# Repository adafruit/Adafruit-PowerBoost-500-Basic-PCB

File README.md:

## Adafruit PowerBoost 500 Basic PCB
<a href="http://www.adafruit.com/products/1903"><br/>
Click here to purchase one from the Adafruit shop</a>

This little DC/DC boost converter module can run from 1.8V batteries or higher, and convert that voltage to 5.2V DC for running your 5V projects. Like our popular 5V 1A USB wall adapter, we tweaked the output to be 5.2V instead of a straight-up 5.0V so that there's a little bit of 'headroom' long cables, high draw, the addition of a diode on the output if you wish, etc. The 5.2V is safe for all 5V-powered electronics like Adafruit Metro/Trinket/Gemma/ItsyBitsy, Arduino, Raspberry Pi, or BeagleBone while preventing icky brown-outs during high current draw because of USB cable resistance.

The PowerBoost 500 has at the heart a TPS61090 boost converter from TI. This boost converter chip has some really nice extras such as low battery detection, 2A internal switch, synchronous conversion, excellent efficiency, and 700KHz high-frequency operation.

These are the Eagle CAD files for the Adafruit Adafruit PowerBoost 500 Basic breakout:
----> https://www.adafruit.com/product/1903

### License

Adafruit invests time and resources providing this open source design, please support Adafruit and open-source hardware by purchasing products from [Adafruit](https://www.adafruit.com)!

All text above must be included in any redistribution

Designed by Limor Fried/Ladyada for Adafruit Industries.
Creative Commons Attribution/Share-Alike, all text above must be included in any redistribution. 
See license.txt for additional information.

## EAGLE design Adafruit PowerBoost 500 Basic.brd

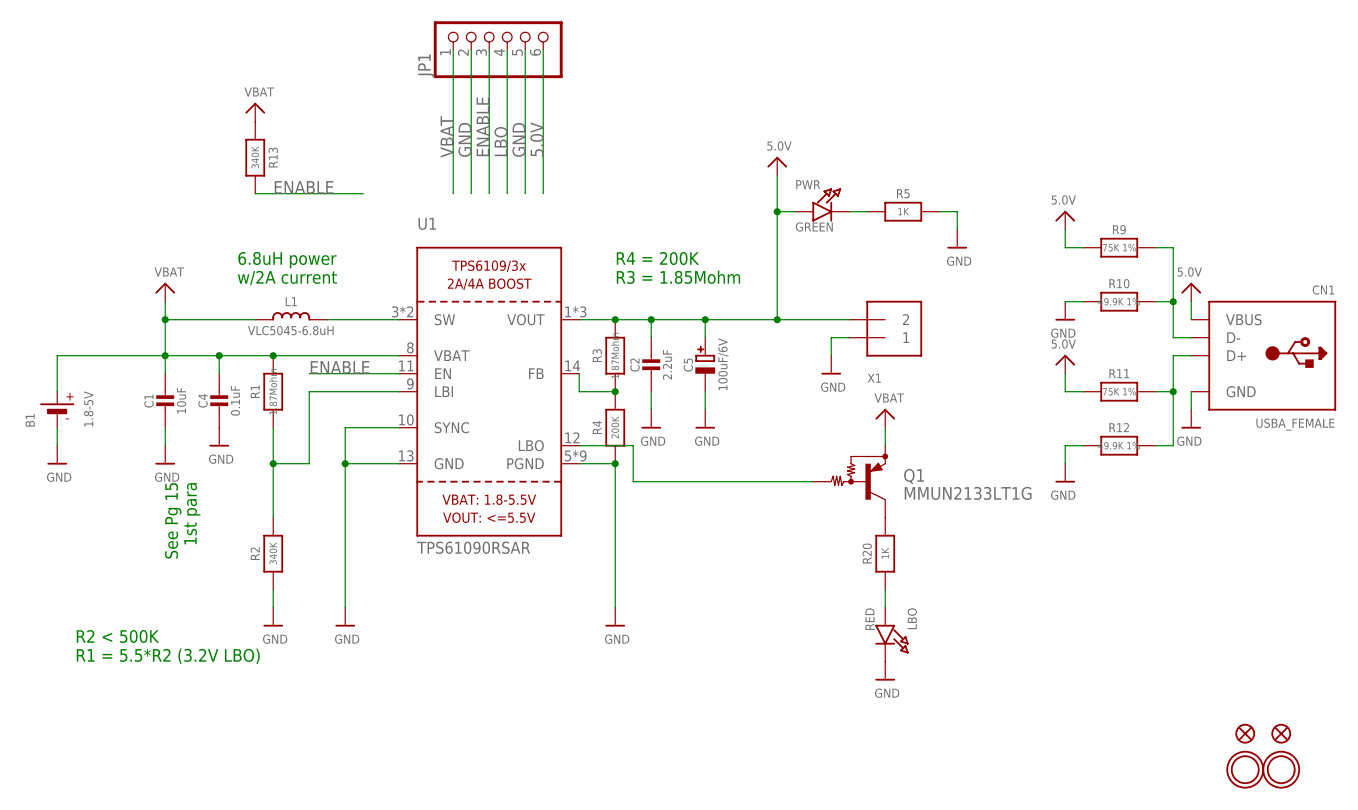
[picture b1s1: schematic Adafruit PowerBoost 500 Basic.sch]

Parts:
B1: 1.8-5V; JSTPH2
C1: 10uF; 0805-NO
C2: 2.2uF; 0805-NO
C4: 0.1uF; 0805-NO
C5: 100uF/6V; EIA3528-21/B-R
CN1: USBA_FEMALE; USB_HOST-PTH
FID2, FID3: FIDUCIAL""; FIDUCIAL_1MM
JP1: PINHD-1X6CB; 1X06-CLEANBIG
L1: VLC5045-6.8uH; INDUCTOR_5X5MM_TDK_VLC5045
LBO: RED; CHIPLED_0805_NOOUTLINE
PWR: GREEN; CHIPLED_0805_NOOUTLINE
Q1: MMUN2133LT1G; SC59-BEC
R1, R3: 1.87Mohm; 0805-NO
R2, R13: 340K; 0805-NO
R4: 200K; 0805-NO
R5, R20: 1K; 0805-NO
R9, R11: 75K 1%; 0805-NO
R10, R12: 49.9K 1%; 0805-NO
U1: TPS61090RSAR; PVQFN-16
U$10, U$12: MOUNTINGHOLE2.5; MOUNTINGHOLE_2.5_PLATED
X1: TERMBLOCK_1X2; TERMBLOCK_1X2-3.5MM

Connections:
5.0V: C2.1, C5.+, CN1.VBUS, JP1.6, PWR.A, R3.2, R9.2, R11.2, U1.1 (VOUT), U1.15 (VOUT), U1.16 (VOUT), X1.2
D+: CN1.D+, R11.1, R12.1
D-: CN1.D-, R9.1, R10.1
ENABLE: JP1.3, R13.2, U1.11 (EN)
GND: B1.1 (-), C1.2, C2.2, C4.2, C5.-, CN1.GND, JP1.2, JP1.5, LBO.C, R2.1, R4.1, R5.2, R10.2, R12.2, U1.5 (PGND), U1.6 (PGND), U1.7 (PGND), U1.10 (SYNC), U1.13 (GND), U1.P$18 (PGND), U1.P$19 (PGND), U1.P$20 (PGND), U1.P$21 (PGND), U1.P$22 (PGND), U1.THERMAL (PGND), X1.1
LBO: JP1.4, Q1.B, U1.12 (LBO)
unnamed: L1.P$2 (2), U1.3 (SW), U1.4 (SW)
unnamed: LBO.A, R20.1
unnamed: R1.1, R2.2, U1.9 (LBI)
unnamed: PWR.C, R5.1
unnamed: R3.1, R4.2, U1.14 (FB)
unnamed: Q1.C, R20.2
VBAT: B1.2 (+), C1.1, C4.1, JP1.1, L1.P$1 (1), Q1.E, R1.2, R13.1, U1.8 (VBAT)

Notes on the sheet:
See Pg 15 1st para
6.8uH power w/2A current
R2 < 500K R1 = 5.5*R2 (3.2V LBO)
R4 = 200K R3 = 1.85Mohm

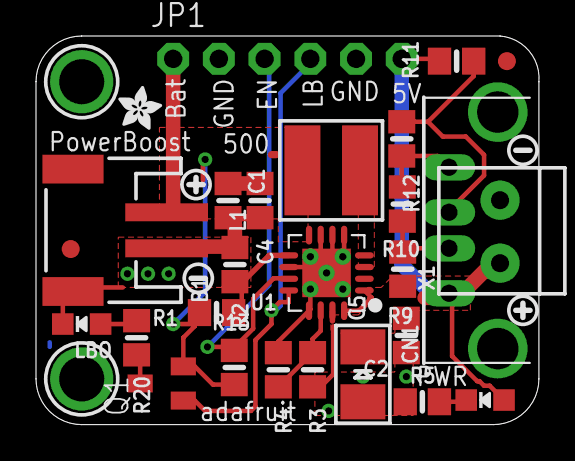
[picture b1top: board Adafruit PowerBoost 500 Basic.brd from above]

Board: 2 copper layers, 27.9 x 21.6 mm, 34 parts (1 on the bottom side), 13 nets.

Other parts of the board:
U$13, U$25: SYMBOL_PLUS
U$23, U$26: SYMBOL_MINUS
U$28: ADAFRUIT_2.5MM
U$29: ADAFRUIT_5MM

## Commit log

2015-01-04 init
2015-01-04 read url

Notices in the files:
parts and their libraries:
microbuilder: This work is placed in the public domain, and may be freely used for commercial and non-commercial work with the following conditions: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
